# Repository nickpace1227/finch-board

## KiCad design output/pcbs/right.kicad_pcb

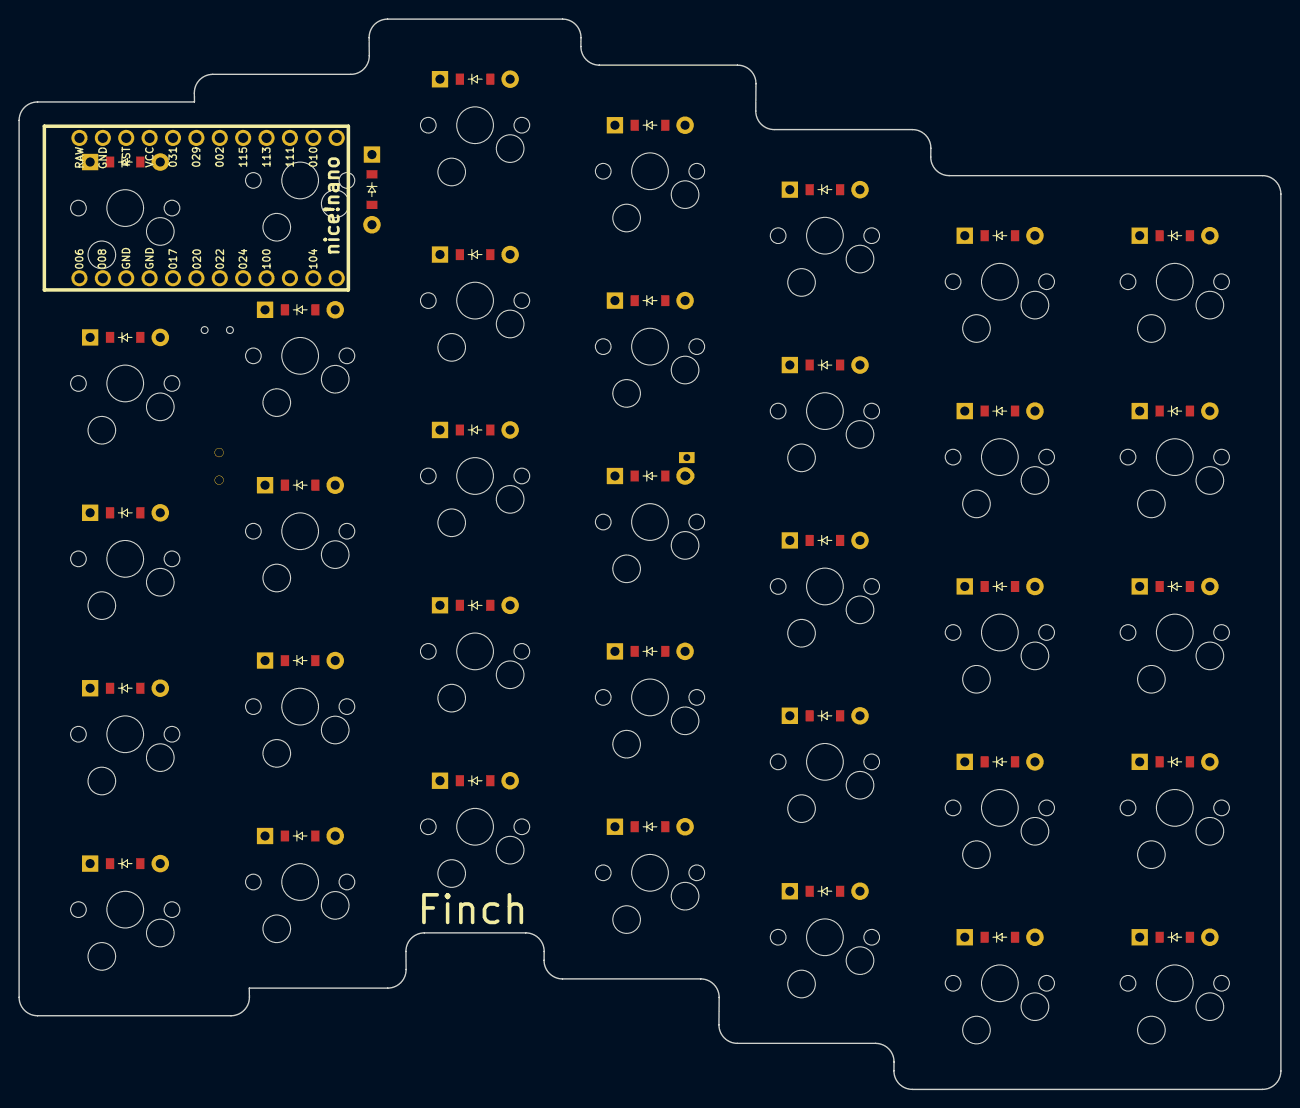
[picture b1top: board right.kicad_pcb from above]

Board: 2 copper layers, 137.0 x 116.2 mm, 74 parts (0 on the bottom side), 51 nets, no tracks yet.

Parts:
B1: Panasonic_EVQPUL_EVQPUC
D1, D2, D3, D4, D5, D6, D7, D8, D9, D10, D11, D12, D13, D14, D15, D16, D17, D18, D19, D20, D21, D22, D23, D24, D25, D26, D27, D28, D29, D30, D31, D32, D33, D34, D35: ComboDiode
JST1: JST_PH_S2B-PH-K_02x2.00mm_Angled
MCU1: nice_nano
S1, S2, S3, S4, S5, S6, S7, S8, S9, S10, S11, S12, S13, S14, S15, S16, S17, S18, S19, S20, S21, S22, S23, S24, S25, S26, S27, S28, S29, S30, S31, S32, S33, S34, S35: MX
T1: SPDT_C128955

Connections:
GND: B1.1, JST1.2, MCU1.3, MCU1.4, MCU1.23
P2: S1.1, S2.1, S3.1, S4.1, S5.1
P3: S6.1, S7.1, S8.1, S9.1, S10.1
P4: S11.1, S12.1, S13.1, S14.1, S15.1
P5: S16.1, S17.1, S18.1, S19.1, S20.1
P6: S21.1, S22.1, S23.1, S24.1, S25.1
P7: S26.1, S27.1, S28.1, S29.1, S30.1
P8: S31.1, S32.1, S33.1, S34.1, S35.1
P15: D5.1, D10.1, D15.1, D20.1, D25.1, D34.1, D35.1
P18: D4.1, D9.1, D14.1, D19.1, D24.1, D29.1, D33.1
P19: D3.1, D8.1, D13.1, D18.1, D23.1, D28.1, D32.1
P20: D2.1, D7.1, D12.1, D17.1, D22.1, D27.1, D31.1
P21: D1.1, D6.1, D11.1, D16.1, D21.1, D26.1, D30.1
RAW: MCU1.24, T1.2
RST: B1.2, MCU1.22
mirror_fifth_bottom: D22.2, S22.2
mirror_fifth_home: D23.2, S23.2
mirror_fifth_mod: D21.2, S21.2
mirror_fifth_num: D25.2, S25.2
mirror_fifth_top: D24.2, S24.2
mirror_first_bottom: D2.2, S2.2
mirror_first_home: D3.2, S3.2
mirror_first_mod: D1.2, S1.2
mirror_first_num: D5.2, S5.2
mirror_first_top: D4.2, S4.2
mirror_fourth_bottom: D17.2, S17.2
mirror_fourth_home: D18.2, S18.2
mirror_fourth_mod: D16.2, S16.2
mirror_fourth_num: D20.2, S20.2
mirror_fourth_top: D19.2, S19.2
mirror_second_bottom: D7.2, S7.2
mirror_second_home: D8.2, S8.2
mirror_second_mod: D6.2, S6.2
mirror_second_num: D10.2, S10.2
mirror_second_top: D9.2, S9.2
mirror_seventh_bottom: D31.2, S32.2
mirror_seventh_home: D32.2, S33.2
mirror_seventh_mod: D30.2, S31.2
mirror_seventh_num: D34.2, S35.2
mirror_seventh_top: D33.2, S34.2
mirror_sixth_bottom: D27.2, S27.2
mirror_sixth_home: D28.2, S28.2
mirror_sixth_mod: D26.2, S26.2
mirror_sixth_num: D35.2, S30.2
mirror_sixth_top: D29.2, S29.2
mirror_third_bottom: D12.2, S12.2
mirror_third_home: D13.2, S13.2
mirror_third_mod: D11.2, S11.2
mirror_third_num: D15.2, S15.2
mirror_third_top: D14.2, S14.2
pos: JST1.1, T1.1

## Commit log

2024-08-12 updated diode pos., controller, and outlines
2024-08-12 Fixed controller position
2024-08-13 fixed diodes in conflict with controller
2024-08-13 Updated diode pos and controller pos on right hand
